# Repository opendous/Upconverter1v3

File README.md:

# Upconverter1v3
Upconverter 125MHz v1.3 - Passive Upconverter Hardware Design for SDR

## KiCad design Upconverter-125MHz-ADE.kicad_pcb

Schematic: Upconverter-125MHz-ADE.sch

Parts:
AG1, AG2: ESD; 0603
BT1: BATTERY; BatteryHolder_2481_4AAA
C1, C2, C3, C4, C5, C6: 0u1RF; 0805
C9: 22uF; 1206
C11, C17: 68pF; 0805
C12: 6pF; 0805
C13, C71, C72, C73, C74, C77: 100pF; 0805
C14, C83: 30pF; 0805
C15: 82pF; 0805
C16, C31: 20pF; 0805
C21, C27: 15pF; 0805
C22, C26: 8pF; 0805
C23, C25: 56pF; 0805
C24: 4.7pF; 0805
C32: 10pF; 0805
C33: DNI; 0805
C51, C52, C53: 4.7uF; 0805
C54: 10uF; 0805
C61, C62, C63, C64, C65, C66, C67, C68: 0.1uF; 0805
C81: 1kpF; 0805
D1, D2, D3, D4: B40; SOD123
D5: POWERED; 0805
D6: A7; SC70-3_SOT-323
D7: D_LED_TRIPLE; 564-0x00_Triple_LED
D8: ZENER; SOD-323
D9: Z5V6; SMA_DO214A_Diode
F1: PTC; 0805
IC1: LLVB; SOT23-5
IC2: LLXB; SOT23-5
IC3: DCE; SOT23-5
IC4: Ar; SOT23-3
IC5: Z5; SC70-6
IC6, IC7: S169; SOT23-6
IC8: C265; SOT23-5
IC9, IC10: LS; SOT363_NXP
IC11: Z5; 000_SC70-6
JP1: EN; SIL-2
JP2: RF_Path_Select; MTS-1x2-C3
JP3, JP4: JUMPER-3; 0603_Jumper
JP5, JP6, JP7: JUMPER-2-NON; SIL-2POS-2mm
JP8: OSC_EN; SIL-2POS-2mm
JP9: JUMPER-3; SIL-3POS-2mm
JP11: JUMPER-2; SIL-2POS-2mm
L9: 47uH; 1206
L12, L32: 150nH; 0805
L14, L22, L26: 110nH; 0805
L16, L31: 120nH; 0805
L21, L27: 56nH; 0805
L23, L25: 15nH; 0805
L24: 180nH; 0805
L33: DNI; 0805
Logo1: Logo; OSHW_Logo
P1: RF; SMA_TH_RA
P2: IF; SMA_TH_RA
P3: OUT; SMA_TH_RA
P4: 12V; SIL-2POS-2mm
P5: OSC; 1Pin_32mil_VIA
P6: BATTERY; SIL-2
R1, R9: 47k; 0805
R8: 680k; 0805
R21, R22, R23, R24: 1k; 0805
R27: 2.5k; 0805
R31, R32, R33, R34, R35, R36: 160; 0805
R41, R42: 36; 0805
R51: 56; 0805
R61, R62: 430; 0805
TP1, TP2, TP3, TP4, TP5: RF-TP; UMCC_RF_PCB_RCPTCL
TP6: CLK; UMCC_RF_PCB_RCPTCL
U1, U4, U5, U6: uF; 0805
U2: USB-B; CONN_USB_B
U3: ADE; MiniCircuits_PL-052
V1, V2, V3, V4, V5, V6, V7, V8, V19, V20, V21, V22, V23, V24, V25, V26, V27, V28, V29, V30, V31, V32, V33, V34, V35, V36, V37, V38, V39, V40, V41, V42, V43, V44, V45, V46, V47, V48, V49, V50, V51, V52, V53, V54, V55, V56, V57, V58, V59, V60, V61, V62, V63, V64, V65, V66, V67, V68, V69, V70, V71, V72, V73, V74, V75, V76, V77, V78, V79, V80, V81, V82, V83, V84, V85, V86, V87, V88, V89, V90, V91, V92, V93, V94, V95, V96, V97, V98, V99, V100, V101, V102, V103, V104, V105, V106, V107, V108, V109, V110, V111, V112, V113, V114, V115, V116, V117, V118, V119, V120, V121, V122, V123, V124, V125, V126, V127, V128, V129, V130, V131, V132, V133, V134, V135, V136, V137, V138, V139, V140, V141, V142, V143, V144, V145, V146, V147, V148, V149, V150, V151, V152, V153, V154, V155, V156, V157, V158, V159, V160, V161, V162, V163, V164, V165, V166, V167, V168, V169, V170, V171, V172, V173, V174, V175, V176, V177, V178, V179, V180, V181, V182, V183, V184, V185, V186, V187, V188, V189, V190, V191, V192, V193, V194, V195, V196, V197, V198, V199, V200, V201, V202, V203, V204, V205, V206, V207, V208, V209, V210, V211, V212, V213, V214, V215, V216, V217, V218, V219, V220, V221, V222, V223, V224, V225, V226, V227, V228, V229, V230, V231, V232, V233, V234, V235, V236, V237, V238, V239, V240, V241, V242, V243, V244, V245, V246, V247, V248, V249, V250, V253, V254, V257, V258, V259, V260, V261, V262, V263, V264, V265, V266, V267, V268, V269, V270, V271, V272, V273, V274, V275, V276, V277, V278, V279, V280, V281, V282, V283, V284, V285, V286, V287, V288, V289, V290, V291, V292, V293, V294, V295, V296, V297, V298, V299, V300, V301, V302, V303, V304, V305, V306, V307, V308, V309, V310, V311, V312, V313, V314, V315, V316, V317, V318, V319, V320, V321, V322, V323, V324, V325, V326, V327, V328, V329, V330, V331, V332, V333, V334, V335, V336, V337, V338, V339, V340, V341, V342, V343, V344, V345, V346, V347, V348, V349, V350, V351, V352, V353, V354, V355, V356, V357, V358, V359, V360, V361, V362, V363, V364, V365, V366, V367, V368, V369, V370, V371, V372, V373, V374, V375, V376, V377, V458, V459, V460, V461, V462, V463, V464, V465, V466, V467, V468, V469, V470, V471, V472, V473, V474, V475, V476, V477, V478, V479, V480, V481, V482, V483, V484, V485, V493, V494, V497, V498, V513, V514, V515, V516, V517, V518, V519, V520, V521, V522, V523, V524: VIA; 1Pin_20mil_VIA
V9, V10, V11, V12, V13, V14, V15, V16, V17, V18: VIA; RF_Mitered_Corner_44mil
V251, V252, V255, V256, V378, V379, V380, V381, V382, V383, V384, V385, V386, V387, V388, V389, V390, V391, V392, V393, V394, V395, V396, V397, V398, V399, V400, V401, V402, V403, V404, V405, V406, V407, V408, V409, V410, V411, V412, V413, V414, V415, V416, V417, V418, V419, V420, V421, V422, V423, V424, V425, V426, V427, V428, V429, V430, V431, V432, V433, V434, V435, V436, V437, V438, V439, V440, V441, V442, V443, V444, V445, V446, V447, V448, V449, V450, V451, V452, V453, V454, V455, V456, V457, V486, V487, V488, V489, V490, V491, V492, V495, V496, V499, V500, V525, V526, V527, V528, V529, V530, V531, V532, V533, V534, V535, V536, V537, V538, V539, V540: VIA; 1Pin_25mil_VIA
V501, V502, V503, V504, V505, V506, V507, V508, V509, V510, V511, V512: VIA; 1Pin_32mil_VIA
X1: 125MHz; Crystal_7x5mm

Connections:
+3.3V: C52.1 (A), C63.1 (A), C64.1 (A), C77.1 (A), D7.6, IC1.5 (OUT), IC5.5 (VCC), IC11.5 (VCC), JP2.3 (B), JP3.2, JP3.3, JP4.1, JP6.1, JP6.2, JP11.1, JP11.2, V253.1, V254.1, V255.1, V256.1, X1.4 (VDD)
+4.5V: C53.1 (A), C65.1 (A), IC2.5 (OUT), IC8.5, JP7.1, JP7.2
+12V: C9.1 (A), C81.1 (A), D4.1, P4.2 (PM), R8.2 (B), R27.2 (B)
/CLK: R36.2 (B), TP6.1 (RF), X1.3 (OUT)
/D_Cathode: C66.1 (A), D8.1, R27.1 (A), TP5.1 (RF), U1.1 (A), V19.1, V466.1
/IF: C16.2 (B), C17.1 (A), L16.1 (A), TP1.1 (RF), U3.2 (IF)
/IF_OUT: AG2.1, C4.2 (B), P2.1 (In)
/LO: C33.1 (A), L32.1 (A), L33.1 (A), TP3.1 (RF), U3.6 (LO), V15.1
/OUT: P3.1 (In), R34.2 (B), R42.1 (A)
/RF: C21.1 (A), C22.1 (A), L21.1 (A), TP2.1 (RF), U3.3 (RF), V12.1
/RF_IN: AG1.1, C1.1 (A), P1.1 (In)
/RF_Passthrough: C6.1 (A), IC6.1 (RF1), V9.1, V10.1
/USB_DN: R35.1 (A), U2.2 (DN)
/USB_DP: R35.2 (B), U2.3 (DP)
/VBUS_CONN: F1.2 (B), U2.1 (VBUS)
GND: AG1.2, AG2.2, BT1.2 (-), C9.2 (B), C11.2 (B), C13.2 (B), C15.2 (B), C17.2 (B), C21.2 (B), C23.2 (B), C25.2 (B), C27.2 (B), C31.2 (B), C33.2 (B), C51.2 (B), C52.2 (B), C53.2 (B), C54.2 (B), C61.2 (B), C62.2 (B), C63.2 (B), C64.2 (B), C65.2 (B), C71.2 (B), C72.2 (B), C73.2 (B), C74.2 (B), C77.2 (B), C83.2 (B), D5.1 (K), D6.1, D6.2, D8.2, D9.2, IC1.2 (GND), IC2.2 (GND), IC3.4, IC4.1 (GND), IC5.2 (GND), IC6.2 (GND), IC7.2 (GND), IC8.3, IC9.2 (GND), IC9.4 (GND), IC9.5 (GND), IC10.2 (GND), IC10.4 (GND), IC10.5 (GND), IC11.2 (GND), IC11.3 (2A), JP2.1 (A), JP2.4 (GND), JP3.1, JP4.2, JP4.3, JP9.1, L21.2 (B), L23.2 (B), L25.2 (B), L27.2 (B), L31.2 (B), L33.2 (B), P1.2 (Ext), P2.2 (Ext), P3.2 (Ext), P4.1, P6.1, R1.1 (A), R9.1 (A), R22.2 (B), R31.1 (A), R32.1 (A), R33.1 (A), R34.1 (A), R51.1 (A), TP1.2 (GND), TP2.2 (GND), TP3.2 (GND), TP4.2 (GND), TP5.2 (GND), TP6.2 (GND), U2.4 (GND), U2.5 (SHIELD), U3.1 (GND), U3.4 (GND), U3.5 (GND), U6.1 (A), V1.1, V2.1, V3.1, V4.1, V5.1, V6.1, V7.1, V8.1, V20.1, V21.1, V22.1, V23.1, V24.1, V25.1, V26.1, V27.1, V28.1, V29.1, V30.1, V31.1, V32.1, V33.1, V34.1, V35.1, V36.1, V37.1, V38.1, V39.1, V40.1, V41.1, V42.1, V43.1, V44.1, V45.1, V46.1, V47.1, V48.1, V49.1, V50.1, V51.1, V52.1, V53.1, V54.1, V55.1, V56.1, V57.1, V58.1, V59.1, V60.1, V61.1, V62.1, V63.1, V64.1, V65.1, V66.1, V67.1, V68.1, V69.1, V70.1, V71.1, V72.1, V73.1, V74.1, V75.1, V76.1, V77.1, V78.1, V79.1, V80.1, V81.1, V82.1, V83.1, V84.1, V85.1, V86.1, V87.1, V88.1, V89.1, V90.1, V91.1, V92.1, V93.1, V94.1, V95.1, V96.1, V97.1, V98.1, V99.1, V100.1, V101.1, V102.1, V103.1, V104.1, V105.1, V106.1, V107.1, V108.1, V109.1, V110.1, V111.1, V112.1, V113.1, V114.1, V115.1, V116.1, V117.1, V118.1, V119.1, V120.1, V121.1, V122.1, V123.1, V124.1, V125.1, V126.1, V127.1, V128.1, V129.1, V130.1, V131.1, V132.1, V133.1, V134.1, V135.1, V136.1, V137.1, V138.1, V139.1, V140.1, V141.1, V142.1, V143.1, V144.1, V145.1, V146.1, V147.1, V148.1, V149.1, V150.1, V151.1, V152.1, V153.1, V154.1, V155.1, V156.1, V157.1, V158.1, V159.1, V160.1, V161.1, V162.1, V163.1, V164.1, V165.1, V166.1, V167.1, V168.1, V169.1, V170.1, V171.1, V172.1, V173.1, V174.1, V175.1, V176.1, V177.1, V178.1, V179.1, V180.1, V181.1, V182.1, V183.1, V184.1, V185.1, V186.1, V187.1, V188.1, V189.1, V190.1, V191.1, V192.1, V193.1, V194.1, V195.1, V196.1, V197.1, V198.1, V199.1, V200.1, V201.1, V202.1, V203.1, V204.1, V205.1, V206.1, V207.1, V208.1, V209.1, V210.1, V211.1, V212.1, V213.1, V214.1, V215.1, V216.1, V217.1, V218.1, V219.1, V220.1, V221.1, V222.1, V223.1, V224.1, V225.1, V226.1, V227.1, V228.1, V229.1, V230.1, V231.1, V232.1, V233.1, V234.1, V235.1, V236.1, V237.1, V238.1, V239.1, V240.1, V241.1, V242.1, V243.1, V244.1, V245.1, V246.1, V247.1, V248.1, V257.1, V258.1, V259.1, V260.1, V261.1, V262.1, V263.1, V264.1, V265.1, V266.1, V267.1, V268.1, V269.1, V270.1, V271.1, V272.1, V273.1, V274.1, V275.1, V276.1, V277.1, V278.1, V279.1, V280.1, V281.1, V282.1, V283.1, V284.1, V285.1, V286.1, V287.1, V288.1, V289.1, V290.1, V291.1, V292.1, V293.1, V294.1, V295.1, V296.1, V297.1, V298.1, V299.1, V300.1, V301.1, V302.1, V303.1, V304.1, V305.1, V306.1, V307.1, V308.1, V309.1, V310.1, V311.1, V312.1, V313.1, V314.1, V315.1, V316.1, V317.1, V318.1, V319.1, V320.1, V321.1, V322.1, V323.1, V324.1, V325.1, V326.1, V327.1, V328.1, V329.1, V330.1, V331.1, V332.1, V333.1, V334.1, V335.1, V336.1, V337.1, V338.1, V339.1, V340.1, V341.1, V342.1, V343.1, V344.1, V345.1, V346.1, V347.1, V348.1, V349.1, V350.1, V351.1, V352.1, V353.1, V354.1, V355.1, V356.1, V357.1, V358.1, V359.1, V360.1, V361.1, V362.1, V363.1, V364.1, V365.1, V366.1, V367.1, V368.1, V369.1, V370.1, V371.1, V372.1, V373.1, V374.1, V375.1, V376.1, V377.1, V378.1, V379.1, V380.1, V381.1, V382.1, V383.1, V384.1, V385.1, V386.1, V387.1, V388.1, V389.1, V390.1, V391.1, V392.1, V393.1, V394.1, V395.1, V396.1, V397.1, V398.1, V399.1, V400.1, V401.1, V402.1, V403.1, V404.1, V405.1, V406.1, V407.1, V408.1, V409.1, V410.1, V411.1, V412.1, V413.1, V414.1, V415.1, V416.1, V417.1, V418.1, V419.1, V420.1, V421.1, V422.1, V423.1, V424.1, V425.1, V426.1, V427.1, V428.1, V429.1, V430.1, V431.1, V432.1, V433.1, V434.1, V435.1, V436.1, V437.1, V438.1, V439.1, V440.1, V441.1, V442.1, V443.1, V444.1, V445.1, V446.1, V447.1, V448.1, V449.1, V450.1, V451.1, V452.1, V453.1, V454.1, V455.1, V456.1, V457.1, V458.1, V459.1, V460.1, V461.1, V462.1, V463.1, V464.1, V465.1, V472.1, V473.1, V474.1, V475.1, V476.1, V477.1, V478.1, V479.1, V480.1, V481.1, V482.1, V483.1, V485.1, V486.1, V487.1, V488.1, V489.1, V490.1, V491.1, V492.1, V501.1, V502.1, V503.1, V504.1, V505.1, V506.1, V507.1, V508.1, V509.1, V510.1, V511.1, V512.1, V513.1, V514.1, V515.1, V516.1, V517.1, V518.1, V519.1, V520.1, V521.1, V522.1, V523.1, V524.1, V525.1, V526.1, V527.1, V528.1, V529.1, V530.1, V531.1, V532.1, V533.1, V534.1, V535.1, V536.1, V537.1, V538.1, V539.1, V540.1, X1.2 (GND)
unnamed: D7.3, R22.1 (A)
unnamed: D7.1, R21.1 (A)
unnamed: IC4.2 (~OUT), R21.2 (B)
unnamed: IC8.2, R36.1 (A)
unnamed: C68.1 (A), IC10.3 (RFout), U5.1 (A), V470.1
unnamed: C67.2 (B), IC10.6 (RFin), U4.2 (B), V469.1
unnamed: C1.2 (B), C2.1 (A), D6.3
unnamed: D4.2, IC3.5, L9.1 (A)
unnamed: IC5.1 (1A), JP2.2 (C), R1.2 (B)
unnamed: D7.5, R62.1 (A)
unnamed: C5.1 (A), C27.1 (A), L26.1 (A), L27.1 (A)
unnamed: D3.2, JP1.1
unnamed: C3.2 (B), C11.1 (A), C12.1 (A), L12.2 (B), V18.1
unnamed: C81.2 (B), IC3.2, R8.1 (A), R9.2 (B)
unnamed: BT1.1 (+), D2.2, P6.2 (PM)
unnamed: C2.2 (B), IC6.5 (RFC)
unnamed: IC11.6 (1Y), R24.1 (A), R61.2 (B)
unnamed: C83.1 (A), IC11.1 (1A), R24.2 (B)
unnamed: P5.1, R51.2 (B), R61.1 (A)
unnamed: C66.2 (B), IC9.6 (RFin), U1.2 (B), V467.1
unnamed: C67.1 (A), IC9.3 (RFout), U4.1 (A), V468.1
unnamed: C68.2 (B), R33.2 (B), R42.2 (B), U5.2 (B), V471.1
unnamed: C26.2 (B), L26.2 (B)
unnamed: C32.2 (B), L32.2 (B)
unnamed: C24.2 (B), L24.2 (B)
unnamed: C22.2 (B), L22.2 (B)
unnamed: C5.2 (B), IC7.1 (RF1)
unnamed: D5.2 (A), R23.1 (A)
unnamed: C3.1 (A), IC6.3 (RF2)
unnamed: C6.2 (B), IC7.3 (RF2)
unnamed: C14.2 (B), C15.1 (A), C16.1 (A), L14.1 (A), L16.2 (B), V11.1
unnamed: C4.1 (A), IC7.5 (RFC)
unnamed: IC8.4, R31.2 (B), R41.2 (B), TP4.1 (RF)
unnamed: C31.1 (A), C32.1 (A), L31.1 (A), R32.2 (B), R41.1 (A), V16.1, V17.1
unnamed: C25.1 (A), C26.1 (A), L24.1 (A), L25.1 (A), V14.1
unnamed: C12.2 (B), C13.1 (A), C14.1 (A), L12.1 (A), L14.2 (B)
unnamed: C23.1 (A), C24.1 (A), L22.1 (A), L23.1 (A), V13.1
OSC_EN: C72.1 (A), C74.1 (A), IC2.3 (EN), IC5.3 (2A), IC5.6 (1Y), IC6.6 (V1), IC7.4 (V2), IC8.1, JP8.1, JP8.2, JP9.2, JP9.3, V249.1, V250.1, V251.1, V252.1, V497.1, V498.1, V499.1, V500.1, X1.1 (EN)
RFS2: C71.1 (A), C73.1 (A), IC5.4 (2Y), IC6.4 (V2), IC7.6 (V1), R62.2 (B), V493.1, V494.1, V495.1, V496.1
VBUS: D1.2, D7.4, F1.1 (A)
VCC: C51.1 (A), C61.1 (A), C62.1 (A), D1.1, D2.1, D7.2, D9.1, IC1.1 (IN), IC1.3 (EN), IC2.1 (IN), IC4.3 (Vcc), JP1.2, JP5.1, JP5.2
VDD_RF: C54.1 (A), D3.1, IC3.1, IC3.3, IC9.1 (VCC), IC10.1 (VCC), L9.2 (B), R23.2 (B), U6.2 (B), V484.1

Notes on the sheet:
Attenuator
6dB
74LVC1G126
74LVC2G14
RF Noise Source
Noise
Bessel Bandpass Filter
USB Power Supply
Oscillator
TPS79333DBV
Elliptic (Cauer) Lowpass Filter
Butterworth Bandpass Filter
Fuse
12V Power Supply
Zener Diodes above 6V use Avalanche Breakdown instead of Zener Breakdown. BZX384-C7V5
The PTC Fuse has about 0.5 Ohm resistance
Avalanche Noise Generator
25V
NCP1403
LP5907MFX-3.3
MBR0540
VC06AG183R0YAT
AntennaGuard
TPS79345DBV
LP5907MFX-4.5
RFS1=High=Passthrough RFS2=Low=Upconvert
Active-Low Reset Monitor will light up Red LED when input voltage drops below 3.5V which means battery or USB power is too low. Otherwise only quiescient current of RF switches and other actives flows when in Passthrough Mode.
BD48K35G-TL
APX809-40SA
MAX809JTRG
JP4 is a trace jumper
Red = Power Supply too Low
Yellow = Powered From USB
Green = Upconverting
8.2pF
6.2pF
For D3 Prefer Low-Leakage SMAZ5V6 is 5uA
Must handle up to 1W = 0.2A * 5.6V
BAV99
BGA2817

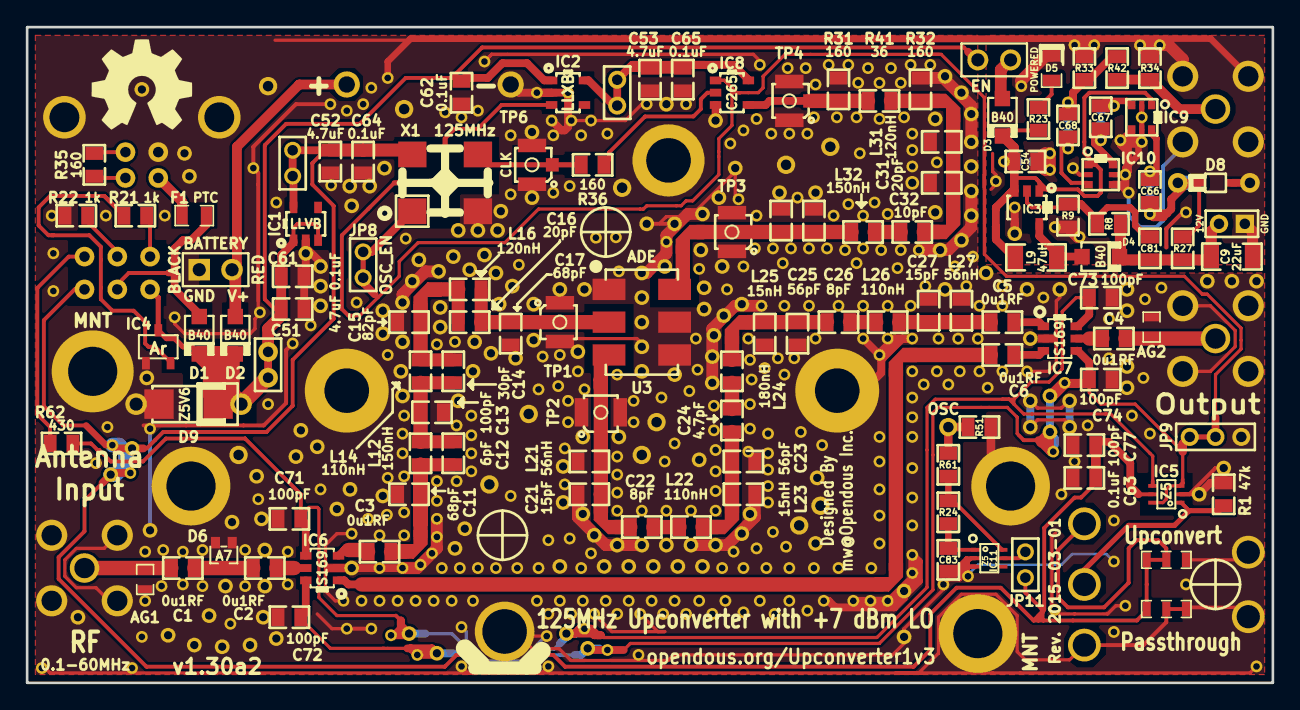
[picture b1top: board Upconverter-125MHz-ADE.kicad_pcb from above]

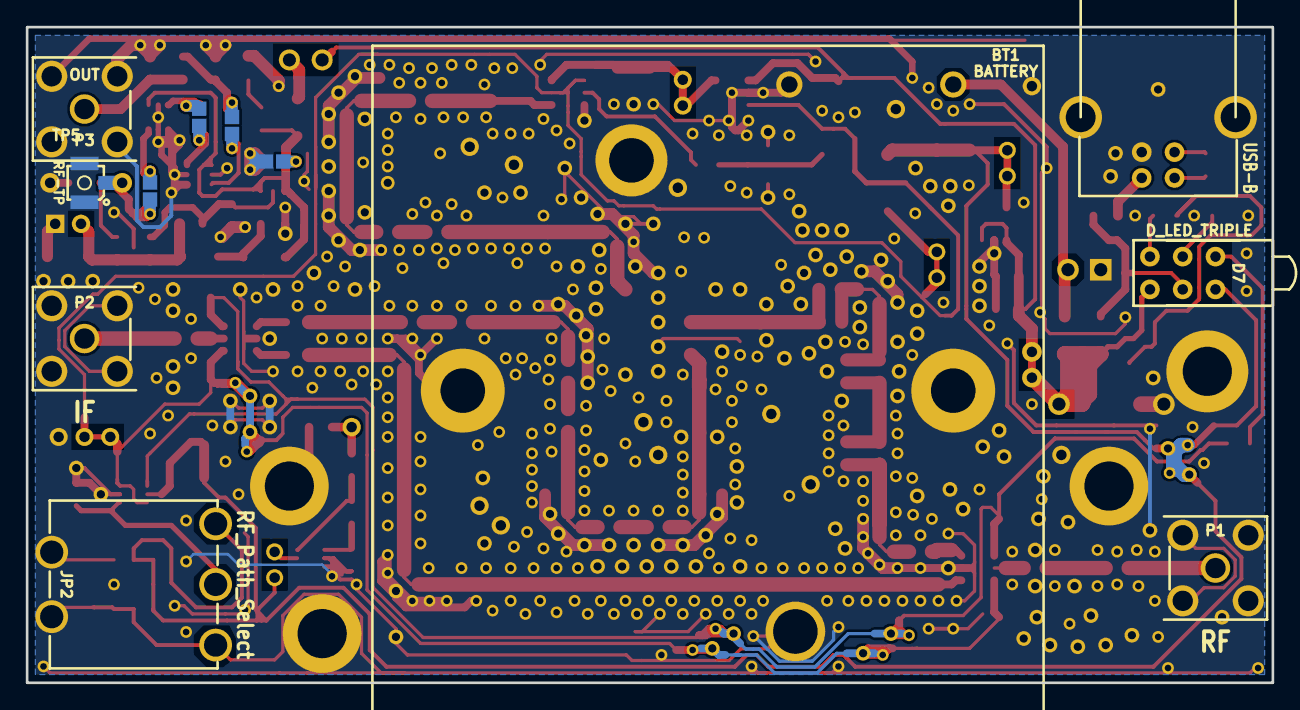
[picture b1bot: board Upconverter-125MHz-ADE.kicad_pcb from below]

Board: 2 copper layers, 96.5 x 50.8 mm, 670 parts (12 on the bottom side), 58 nets.

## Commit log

2015-09-15 Upconverter v1.3 Production Design Gerbers Bill Of Materials

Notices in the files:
Upconverter-125MHz-ADE.kicad_pcb:
Opendous Inc. deeded this hardware design into the Public Domain
No Copyright - Deeded under the Creative Commons CC0 Public Domain Dedication
Upconverter-125MHz-ADE.sch:
http://creativecommons.org/publicdomain/zero/1.0
